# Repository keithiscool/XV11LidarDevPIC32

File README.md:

This project uses the XV11 Lidar from a Neato Vacuum Cleaner to track a robot in an 4meter x 8meter arena
The object tracking uses the robot reflectance in order to only track reflective surfaces and objects that are far away from the walls
The MPLabX project "lidarpic_FloatingPoint.X" in the software folder uses a PIC32MX575F512H-80I/PT (ordered from Digikey) micro-controller running at 80MHz
The hardware PCB used is the "FAB_xv11_lidar_dev_2016_01_24" EagleCAD file located in the Hardware folder.

Note: you need to use an FTDI chip to debug the project.
Look at the 6 pin (looks like Arduino ISP header. 
FTDI board rx pin goes to Uart 6 on pic32
Ground goes to ground on the same 6 pin header

Next, run a serial debugger program on your pc like realterm, teraterm, arduino to debug the UART line from the pic32
Also double check the lidar is connected.
The headers are loose on the pic32 header for UART4. hook lidar brown/yellow wire (Lidar tx) to the pic32 (UART4RX). Hook up the lidar power and ground.

The MOSFET and Diode that are being pulsed use the circuit in the included PDF: "Lidar Development Using PIC32MX Microcontroller"
Next hook up the motor power to the +5V pin next to the air wired mosfet.
YOU WILL HAVE TO REPROGRAM THE pic32 when you first power it on with the pickit3 programmer. The pic32 will stop spinning the lidar until the pic32 is re-programmed.

I recommend you make the following changes for the Wii Camera/Lidar board.
1) Add 3.3V pin for Wii Cameras
2) Choose a pic32MX with more independent timers (1 or 2 more 16 bit timers) - the pic32 only has 4 independent timers
3) Switching buck converters (switching down power converters) to help with battery efficiency
4) Add more output capacitance for voltage LDO regulators if you do not use a switching regulator
5) Beef up 3.3V trace on board
6) Place 5V power for lidar next to lidar input pins (place +5V next to UA4RX)

7) Choose an isolated mosfet driver (the one we used was not isolated (grounds were tied  too much noise)
8) Integrate a large mosfet onto the board and use the mosfet driver with it with the attached circuit (see attachment)
9) Choosing locking connectors OR solder all wires to board
10) Move programming header closer to pic32 and avoid meandering traces under & over board

Recommendations:
11) Add a non-ultrasonic distance meter to help with backing up the robot
12) Get ultra-reflective surfaces for TRACEE to help with LIDAR (Aluminum reflectance varied too much from 70 to 130 quality)
13) Use a Gimbal/gyro on the Lidar to help keep it level with arena sand
14) Lower Lidar to sit in the arena like I left it (this will prevent false positives from the judges
15) Look into dust tolerance methods for Lidar (static electricity/magnetism/sound vibrations/solenoid)

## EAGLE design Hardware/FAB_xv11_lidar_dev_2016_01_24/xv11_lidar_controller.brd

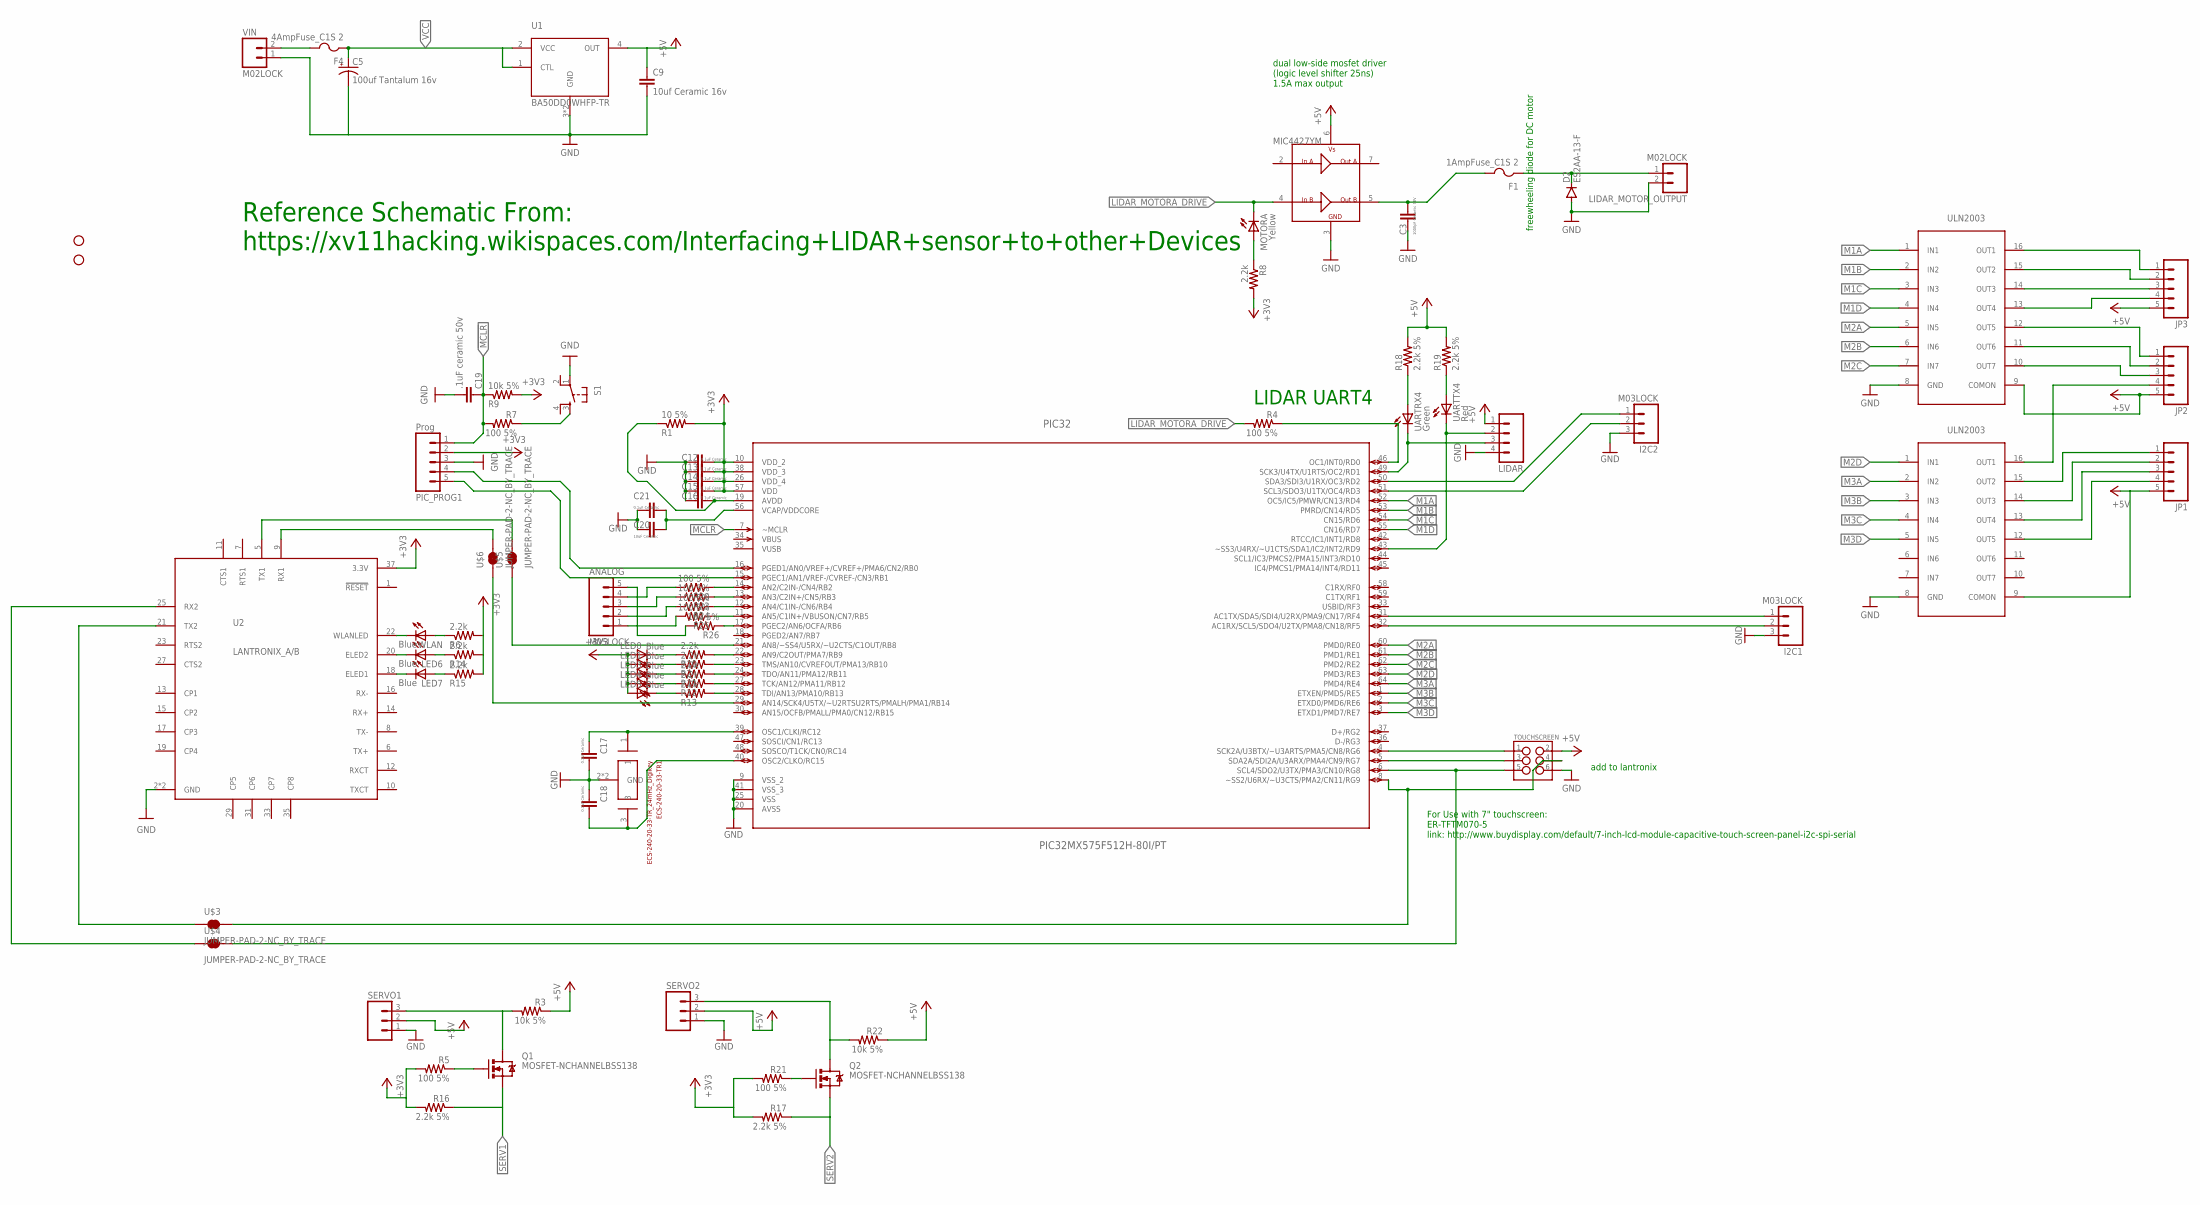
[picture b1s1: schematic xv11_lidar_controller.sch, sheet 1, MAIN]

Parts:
ANALOG: M05LOCK; 1X05_LOCK
C3: 1000pF Ceramic 50V; 0805
C5: 100uf Tantalum 16v; EIA3216
C9: 10uf Ceramic 16v; 0805
C12, C13, C14, C15, C16, C17, C18, C21: 0.1uF Ceramic; 0805
C19: .1uF ceramic 50v; 0805
C20: 10uF Ceramic; 0805
D2: ES2AA-13-F; SMA-DIODE
ECS-240-20-33-TR1: ECS-240-20-33-TR_24mHz_Digikey; ECX-32
F1: 1AmpFuse_C1S 2; R1206
F4: 4AmpFuse_C1S 2; R1206
I2C1, I2C2: M03LOCK; 1X03_LOCK
JP1, JP2, JP3: M05LOCK; 1X05_LOCK
LED0, LED1, LED3, LED4, LED5, LED6, LED7: Blue; CHIP-LED0805
LIDAR: M04LOCK; 1X04_LOCK
LIDAR_MOTOR_OUTPUT: M02LOCK; 1X02_LOCK
MOTORA: Yellow; CHIP-LED0805
PIC32: PIC32MX575F512H-80I/PT; QFP50P1200X1200X120-64N
PIC_PROG1: Prog; 1X05_LOCK_LONGPADS
Q1, Q2: MOSFET-NCHANNELBSS138; SOT23
R1: 10 5%; R0805
R2, R6, R10, R11, R12, R13, R14, R15: 2.2k; R0805
R3, R9, R22: 10k 5%; R0805
R4: 100 5%; M0805
R5, R7, R20, R21, R23, R24, R25, R26: 100 5%; R0805
R8: 2.2k; M0805
R16, R17: 2.2k 5%; R0805
R18, R19: 2.2k 5%; M0805
S1: TAC_SWITCHSMD; TACTILE-SWITCH-SMD
SERVO1, SERVO2: M03PTH; 1X03
STANDOFF1, STANDOFF2: STAND-OFF
TOUCHSCREEN: M03X2NO_SILK; 2X3-NS
U1: BA50DD0WHFP-TR; HRP5
U2: LANTRONIX_A/B; LANA/BTH
U3: MIC4427YM; SO-08
U$1, U$2: ULN2003; SOIC16_3.9WIDE
U$3, U$4, U$5, U$6: JUMPER-PAD-2-NC_BY_TRACE; PAD-JUMPER-2-NC_BY_TRACE_YES_SILK
UARTRX4: Green; CHIP-LED0805
UARTTX4: Red; CHIP-LED0805
VIN: M02LOCK; 1X02_LOCK
WLAN: Blue; CHIP-LED0805

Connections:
!MCLR: C19.1, PIC32.7 (~MCLR), PIC_PROG1.1, R7.2, R9.1
+3V3: C12.2, C13.2, C14.2, C15.2, LED0.A, LED1.A, LED3.A, LED4.A, LED5.A, PIC32.10 (VDD_2), PIC32.26 (VDD_4), PIC32.38 (VDD_3), PIC32.57 (VDD), PIC_PROG1.2, R1.2, R5.2, R6.2, R8.2, R9.2, R14.2, R15.2, R16.2, R17.2, R21.2, U2.37 (3.3V); also elsewhere on the board
+5V: C9.1, JP1.5, JP2.5, JP3.5, LIDAR.1, R3.1, R18.2, R19.2, R22.1, SERVO1.2, SERVO2.2, TOUCHSCREEN.2, U1.4 (OUT), U3.6 (VS), U$1.9 (COMON), U$2.9 (COMON)
GND: C3.1, C5.C (-), C9.2, C12.1, C13.1, C14.1, C15.1, C16.1, C17.2, C18.1, C19.2, C20.1, C21.1, D2.A, ECS-240-20-33-TR1.2 (GND), ECS-240-20-33-TR1.4 (GND), I2C1.3, I2C2.3, LIDAR.4, LIDAR_MOTOR_OUTPUT.2, PIC32.9 (VSS_2), PIC32.20 (AVSS), PIC32.25 (VSS), PIC32.41 (VSS_3), PIC_PROG1.3, S1.1, SERVO1.1, SERVO2.1, TOUCHSCREEN.6, U1.3 (GND), U1.G (GND), U2.2 (GND), U2.39 (GND), U3.3 (GND), U$1.8 (GND), U$2.8 (GND), VIN.1; also elsewhere on the board
LIDAR_MOTORA_DRIVE: MOTORA.C, R4.2, U3.4 (INB)
LIDAR_MOTOR_OUTPUT: D2.C, F1.1, LIDAR_MOTOR_OUTPUT.1
M1A: PIC32.52 (OC5/IC5/PMWR/CN13/RD4), U$1.1 (IN1)
M1B: PIC32.53 (PMRD/CN14/RD5), U$1.2 (IN2)
M1C: PIC32.54 (CN15/RD6), U$1.3 (IN3)
M1D: PIC32.55 (CN16/RD7), U$1.4 (IN4)
M2A: PIC32.60 (PMD0/RE0), U$1.5 (IN5)
M2B: PIC32.61 (PMD1/RE1), U$1.6 (IN6)
M2C: PIC32.62 (PMD2/RE2), U$1.7 (IN7)
M2D: PIC32.63 (PMD3/RE3), U$2.1 (IN1)
M3A: PIC32.64 (PMD4/RE4), U$2.2 (IN2)
M3B: PIC32.1 (ETXEN/PMD5/RE5), U$2.3 (IN3)
M3C: PIC32.2 (ETXD0/PMD6/RE6), U$2.4 (IN4)
M3D: PIC32.3 (ETXD1/PMD7/RE7), U$2.5 (IN5)
N1: PIC32.22 (AN9/C2OUT/PMA7/RB9), R10.2
N2: PIC32.23 (TMS/AN10/CVREFOUT/PMA13/RB10), R2.2
unnamed: U2.25 (RX2), U$4.1
unnamed: ANALOG.1, R25.2
unnamed: ANALOG.2, R24.2
unnamed: C3.2, F1.2, U3.5 (OUTB)
unnamed: PIC32.46 (OC1/INT0/RD0), R4.1
unnamed: PIC32.14 (AN2/C2IN-/CN4/RB2), R20.1
unnamed: U2.21 (TX2), U$3.1
unnamed: R18.1, UARTRX4.A
unnamed: ANALOG.3, R23.2
unnamed: PIC32.13 (AN3/C2IN+/CN5/RB3), R23.1
unnamed: C17.1, ECS-240-20-33-TR1.1, PIC32.39 (OSC1/CLKI/RC12)
unnamed: C18.2, ECS-240-20-33-TR1.3, PIC32.40 (OSC2/CLKO/RC15)
unnamed: PIC32.12 (AN4/C1IN-/CN6/RB4), R24.1
unnamed: PIC32.11 (AN5/C1IN+/VBUSON/CN7/RB5), R25.1
unnamed: ANALOG.4, R20.2
unnamed: C16.2, PIC32.19 (AVDD), R1.1
unnamed: C20.2, C21.2, PIC32.56 (VCAP/VDDCORE)
unnamed: Q1.3 (D), R3.2, SERVO1.3
unnamed: PIC32.16 (PGED1/AN0/VREF+/CVREF+/PMA6/CN2/RB0), PIC_PROG1.4
unnamed: LED0.C, R10.1
unnamed: PIC32.8 (~SS2/U6RX/~U3CTS/PMA2/CN11/RG9), TOUCHSCREEN.4, U$3.2
unnamed: LED1.C, R2.1
unnamed: R7.1, S1.3
unnamed: LED3.C, R11.1
unnamed: Q2.3 (D), R22.2, SERVO2.3
unnamed: Q1.1 (G), R5.1
unnamed: Q2.1 (G), R21.1
unnamed: LIDAR.3, PIC32.49 (SCK3/U4TX/U1RTS/OC2/RD1), UARTRX4.C
unnamed: LIDAR.2, PIC32.43 (~SS3/U4RX/~U1CTS/SDA1/IC2/INT2/RD9), UARTTX4.C
unnamed: MOTORA.A, R8.1
unnamed: PIC32.24 (TDO/AN11/PMA12/RB11), R11.2
unnamed: PIC32.17 (PGEC2/AN6/OCFA/RB6), R26.1
unnamed: ANALOG.5, R26.2
unnamed: U2.9 (RX1), U$6.2
unnamed: PIC32.21 (AN8/~SS4/U5RX/~U2CTS/C1OUT/RB8), U$5.1
unnamed: R19.1, UARTTX4.A
unnamed: F4.2, VIN.2
unnamed: JP3.1, U$1.16 (OUT1)
unnamed: JP3.2, U$1.15 (OUT2)
unnamed: JP3.3, U$1.14 (OUT3)
unnamed: JP3.4, U$1.13 (OUT4)
unnamed: JP2.1, U$1.12 (OUT5)
unnamed: JP2.2, U$1.11 (OUT6)
unnamed: JP2.3, U$1.10 (OUT7)
unnamed: JP2.4, U$2.16 (OUT1)
unnamed: JP1.1, U$2.15 (OUT2)
unnamed: JP1.2, U$2.14 (OUT3)
unnamed: JP1.3, U$2.13 (OUT4)
unnamed: JP1.4, U$2.12 (OUT5)
unnamed: U2.5 (TX1), U$5.2
unnamed: I2C2.1, PIC32.50 (SDA3/SDI3/U1RX/OC3/RD2)
unnamed: I2C2.2, PIC32.51 (SCL3/SDO3/U1TX/OC4/RD3)
unnamed: PIC32.29 (AN14/SCK4/U5TX/~U2RTSU2RTS/PMALH/PMA1/R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), U$6.1
unnamed: U2.22 (WLANLED), WLAN.C
unnamed: LED6.C, U2.20 (ELED2)
unnamed: LED7.C, U2.18 (ELED1)
unnamed: LED7.A, R15.1
unnamed: LED6.A, R14.1
unnamed: R6.1, WLAN.A
ONE: LED5.C, R13.1
PICUART_RX: I2C1.1, PIC32.31 (AC1TX/SDA5/SDI4/U2RX/PMA9/CN17/RF4)
PICUART_TX: I2C1.2, PIC32.32 (AC1RX/SCL5/SDO4/U2TX/PMA8/CN18/RF5)
PIC_HANG_CHK: PIC32.15 (PGEC1/AN1/VREF-/CVREF-/CN3/RB1), PIC_PROG1.5
SCK2: PIC32.4 (SCK2A/U3BTX/~U3ARTS/PMA5/CN8/RG6), TOUCHSCREEN.1
SDI2: PIC32.5 (SDA2A/SDI2A/U3ARX/PMA4/CN9/RG7), TOUCHSCREEN.3
SDO2: PIC32.6 (SCL4/SDO2/U3TX/PMA3/CN10/RG8), TOUCHSCREEN.5, U$4.2
SERV1: PIC32.28 (TDI/AN13/PMA10/RB13), Q1.2 (S), R13.2, R16.1
SERV2: PIC32.27 (TCK/AN12/PMA11/RB12), Q2.2 (S), R12.2, R17.1
TWO: LED4.C, R12.1
VCC: C5.A (+), F4.1, U1.1 (CTL), U1.2 (VCC); also elsewhere on the board
VUSB: PIC32.35 (VUSB)

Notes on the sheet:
Reference Schematic From: https://xv11hacking.wikispaces.com/Interfacing+LIDAR+sensor+to+other+Devices
freewheeling diode for DC motor
LIDAR UART4
dual low-side mosfet driver (logic level shifter 25ns) 1.5A max output
For Use with 7" touchscreen: ER-TFTM070-5 link: http://www.buydisplay.com/default/7-inch-lcd-module-capacitive-touch-screen-panel-i2c-spi-serial
add to lantronix

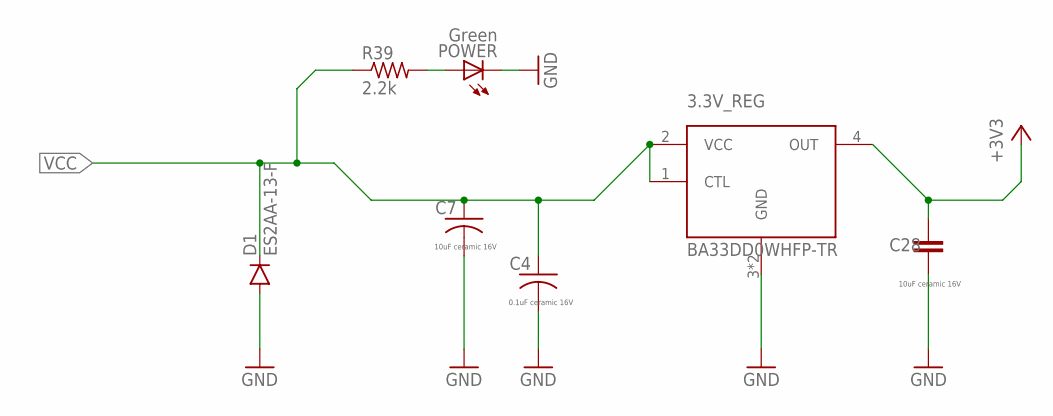
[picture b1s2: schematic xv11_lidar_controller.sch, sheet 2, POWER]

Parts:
3.3V_REG: BA33DD0WHFP-TR; HRP5
C4: 0.1uF ceramic 16V; C0805K
C7: 10uF ceramic 16V; C0805K
C28: 10uF ceramic 16V; 0805
D1: ES2AA-13-F; SMA-DIODE
POWER: Green; CHIP-LED0805
R39: 2.2k; R0805

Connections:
+3V3: 3.3V_REG.4 (OUT), C28.1; also elsewhere on the board
GND: 3.3V_REG.3 (GND), 3.3V_REG.G (GND), C4.2, C7.2, C28.2, D1.A, POWER.C; also elsewhere on the board
unnamed: POWER.A, R39.2
VCC: 3.3V_REG.1 (CTL), 3.3V_REG.2 (VCC), C4.1, C7.1, D1.C, R39.1; also elsewhere on the board

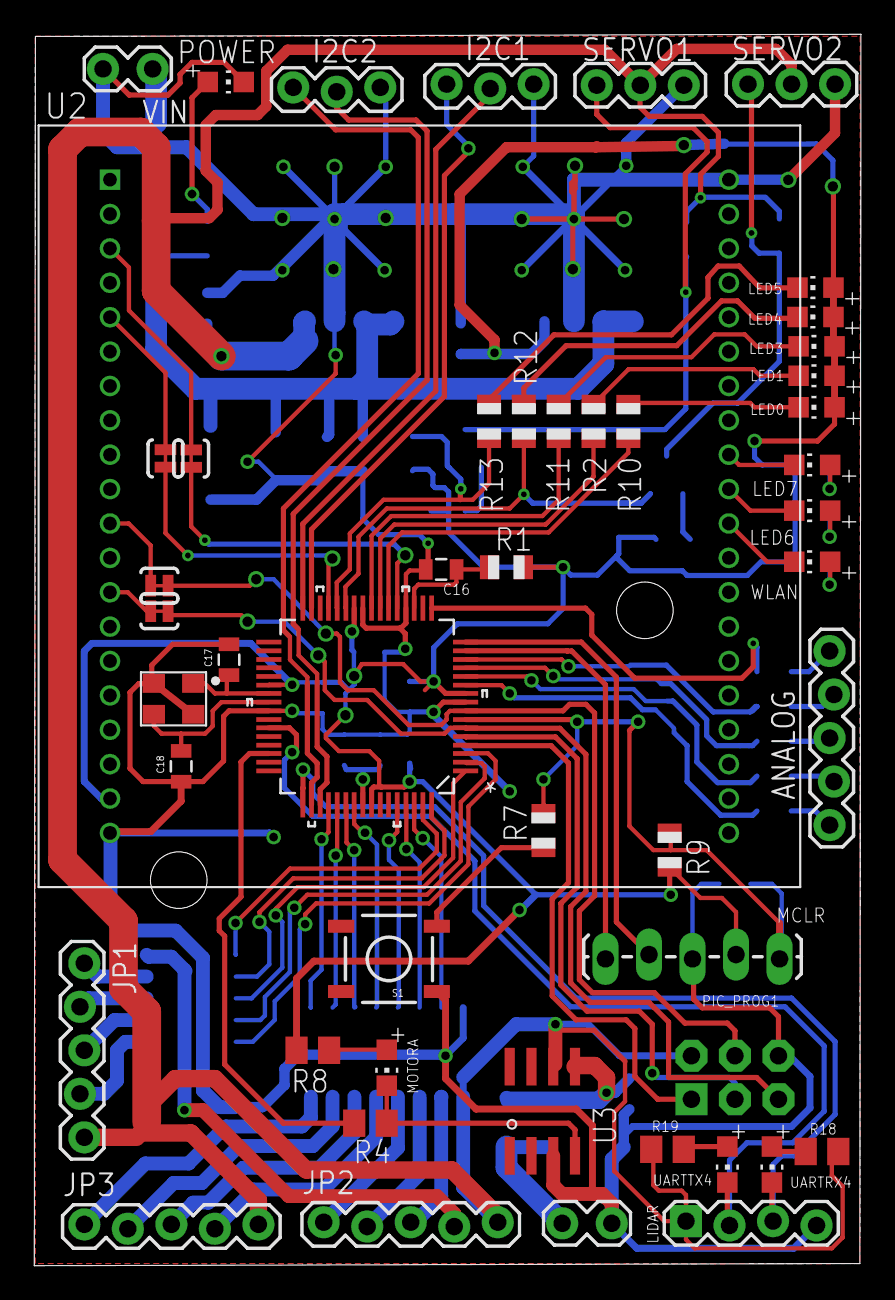
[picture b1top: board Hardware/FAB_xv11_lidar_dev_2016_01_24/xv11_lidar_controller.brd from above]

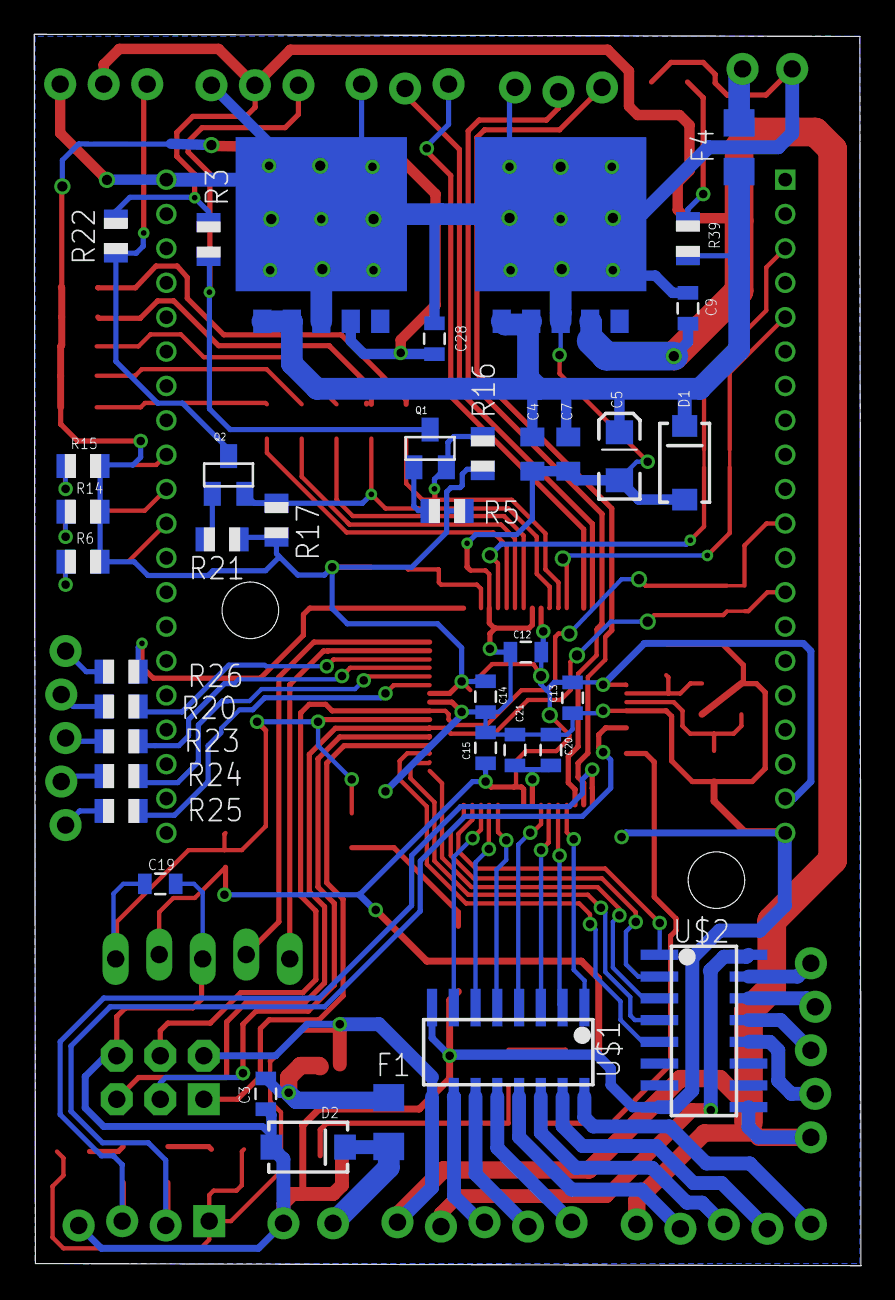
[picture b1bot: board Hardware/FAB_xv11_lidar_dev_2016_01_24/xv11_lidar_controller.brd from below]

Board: 2 copper layers, 48.2 x 71.9 mm, 89 parts (38 on the bottom side), 91 nets.

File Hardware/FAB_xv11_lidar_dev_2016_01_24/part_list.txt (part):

Partlist

Exported from xv11_lidar_controller.brd at 4/28/2016 9:19:55 PM

EAGLE Version 6.5.0 Copyright (c) 1988-2013 CadSoft

Assembly variant: 

Part               Value                          Package                           Library                        Position (mil)        Orientation

3.3V_REG           BA33DD0WHFP-TR                 HRP5                              NASA_LIB                       (1240 2170)           MR0
ANALOG             M05LOCK                        1X05_LOCK                         SparkFun-Connectors            (1832.5 1012.5)       R90
C3                 1000pF Ceramic 50V             0805                              SparkFun-Capacitors            (1367.5 395)          MR90
C4                 0.1uF ceramic 16V              C0805K                            adafruit                       (755 1865)            MR270
C5                 100uf Tantalum 16v             EIA3216                           SparkFun-Capacitors            (555 1860)            MR90
C7                 10uF ceramic 16V               C0805K                            adafruit                       (672.5 1865)          MR270
C9                 10uf Ceramic 16v               0805                              SparkFun-Capacitors            (397.5 2200)          MR90
C12                0.1uF Ceramic                  0805                              SparkFun-Capacitors            (770 1410)            MR0
C13                0.1uF Ceramic                  0805                              SparkFun-Capacitors            (662.5 1305)          MR90
C14                0.1uF Ceramic                  0805                              SparkFun-Capacitors            (862.5 1307.5)        MR90
C15                0.1uF Ceramic                  0805                              SparkFun-Capacitors            (862.5 1190)          MR270
C16                0.1uF Ceramic                  0805                              SparkFun-Capacitors            (935 1600)            R0
C17                0.1uF Ceramic                  0805                              SparkFun-Capacitors            (447.5 1392.5)        R90
C18                0.1uF Ceramic                  0805                              SparkFun-Capacitors            (337.5 1147.5)        R90
C19                .1uF ceramic 50v               0805                              SparkFun-Capacitors            (1610 877.5)          MR0
C20                10uF Ceramic                   0805                              SparkFun-Capacitors            (712.5 1185)          MR270
C21                0.1uF Ceramic                  0805                              SparkFun-Capacitors            (795 1185)            MR270
C28                10uF ceramic 16V               0805                              SparkFun-Capacitors            (980 2130)            MR90
D1                 ES2AA-13-F                     SMA-DIODE                         SparkFun-DiscreteSemi          (405 1845)            MR90
D2                 ES2AA-13-F                     SMA-DIODE                         SparkFun-DiscreteSemi          (1270 272.5)          MR0
ECS-240-20-33-TR1  ECS-240-20-33-TR_24mHz_Digikey ECX-32                            Crystal ECS                    (320 1302.5)          R180
F1                 1AmpFuse_C1S 2                 R1206                             adafruit                       (1085 330)            MR90
F4                 4AmpFuse_C1S 2                 R1206                             adafruit                       (280 2570)            MR90
I2C1               M03LOCK                        1X03_LOCK                         SparkFun-Connectors            (947.5 2710)          R0
I2C2               M03LOCK                        1X03_LOCK                         SparkFun-Connectors            (595 2702.5)          R0
JP1                                               1X05_LOCK                         SparkFun-Connectors            (110 695)             R270
JP2                                               1X05_LOCK                         SparkFun-Connectors            (665 95)              R0
JP3                                               1X05_LOCK                         SparkFun-Connectors            (115 90)              R0
LED0               Blue                           CHIP-LED0805                      adafruit                       (1797.5 1972.5)       R90
LED1               Blue                           CHIP-LED0805                      adafruit                       (1797.5 2045)         R90
LED3               Blue                           CHIP-LED0805                      adafruit                       (1797.5 2112.5)       R90
LED4               Blue                           CHIP-LED0805                      adafruit                       (1795 2180)           R90
LED5               Blue                           CHIP-LED0805                      adafruit                       (1795 2247.5)         R90
LED6               Blue                           CHIP-LED0805                      adafruit                       (1787.5 1735)         R90
LED7               Blue                           CHIP-LED0805                      adafruit                       (1787.5 1840)         R90
LIDAR                                             1X04_LOCK                         SparkFun-Connectors            (1497.5 97.5)         R0
LIDAR_MOTOR_OUTPUT M02LOCK                        1X02_LOCK                         SparkFun-Connectors            (1220 97.5)           R0
MOTORA             Yellow                         CHIP-LED0805                      adafruit                       (810 455)             R180
PIC32              PIC32MX575F512H-80I/PT         QFP50P1200X1200X120-64N           Microchip_By_element14_Batch_1 (765 1285)            R180
PIC_PROG1          Prog                           1X05_LOCK_LONGPADS                SparkFun-Connectors            (1712.5 705)          R180
POWER              Green                          CHIP-LED0805                      adafruit                       (440 2720)            R270
Q1                 MOSFET-NCHANNELBSS138          SOT23                             SparkFun-DiscreteSemi          (990 1878)            MR0
Q2                 MOSFET-NCHANNELBSS138          SOT23                             SparkFun-DiscreteSemi          (1453 1817)           MR0
R1                 10 5%                          R0805                             adafruit                       (1085 1605)           R0
R2                 2.2k                           R0805                             adafruit                       (1285 1940)           R270
R3                 10k 5%                         R0805                             adafruit                       (1499 2358)           MR270
R4                 100 5%                         M0805                             adafruit                       (772.5 327.5)         R0
R5                 100 5%                         R0805                             adafruit                       (951 1734)            MR0
R6                 2.2k                           R0805                             adafruit                       (1787.5 1617.5)       MR0
R7                 100 5%                         R0805                             adafruit                       (1170 1000)           R90
R8                 2.2k                           M0805                             adafruit                       (640 495)             R180
R9                 10k 5%                         R0805                             adafruit                       (1460 955)            R270
R10                2.2k                           R0805                             adafruit                       (1365 1940)           R270
R11                2.2k                           R0805                             adafruit                       (1205 1940)           R270
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
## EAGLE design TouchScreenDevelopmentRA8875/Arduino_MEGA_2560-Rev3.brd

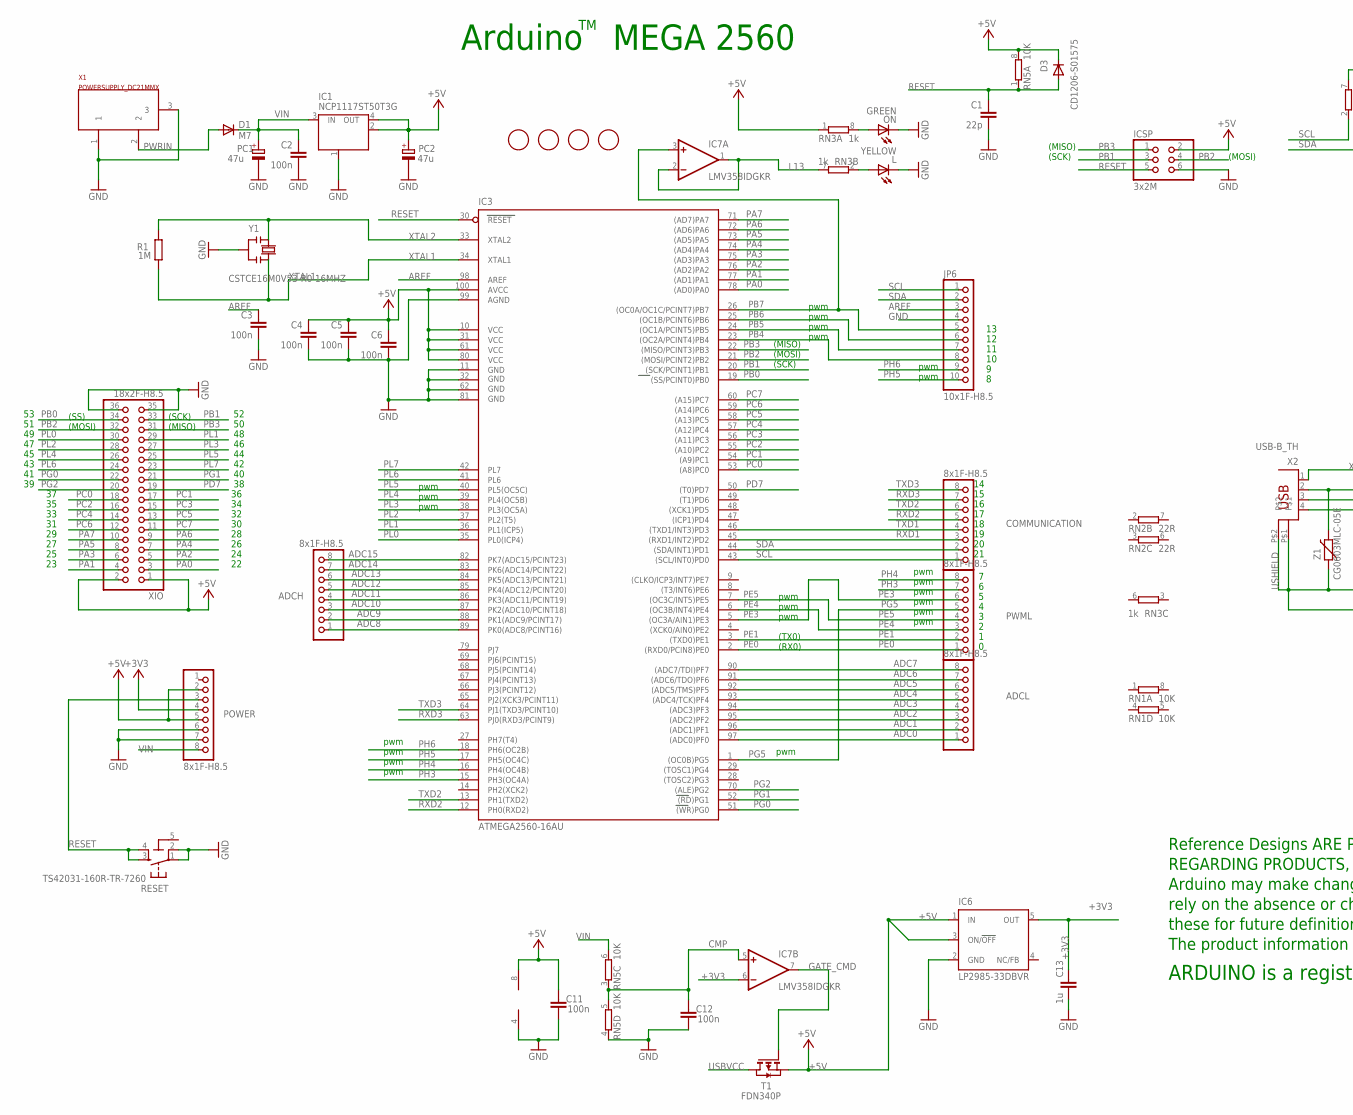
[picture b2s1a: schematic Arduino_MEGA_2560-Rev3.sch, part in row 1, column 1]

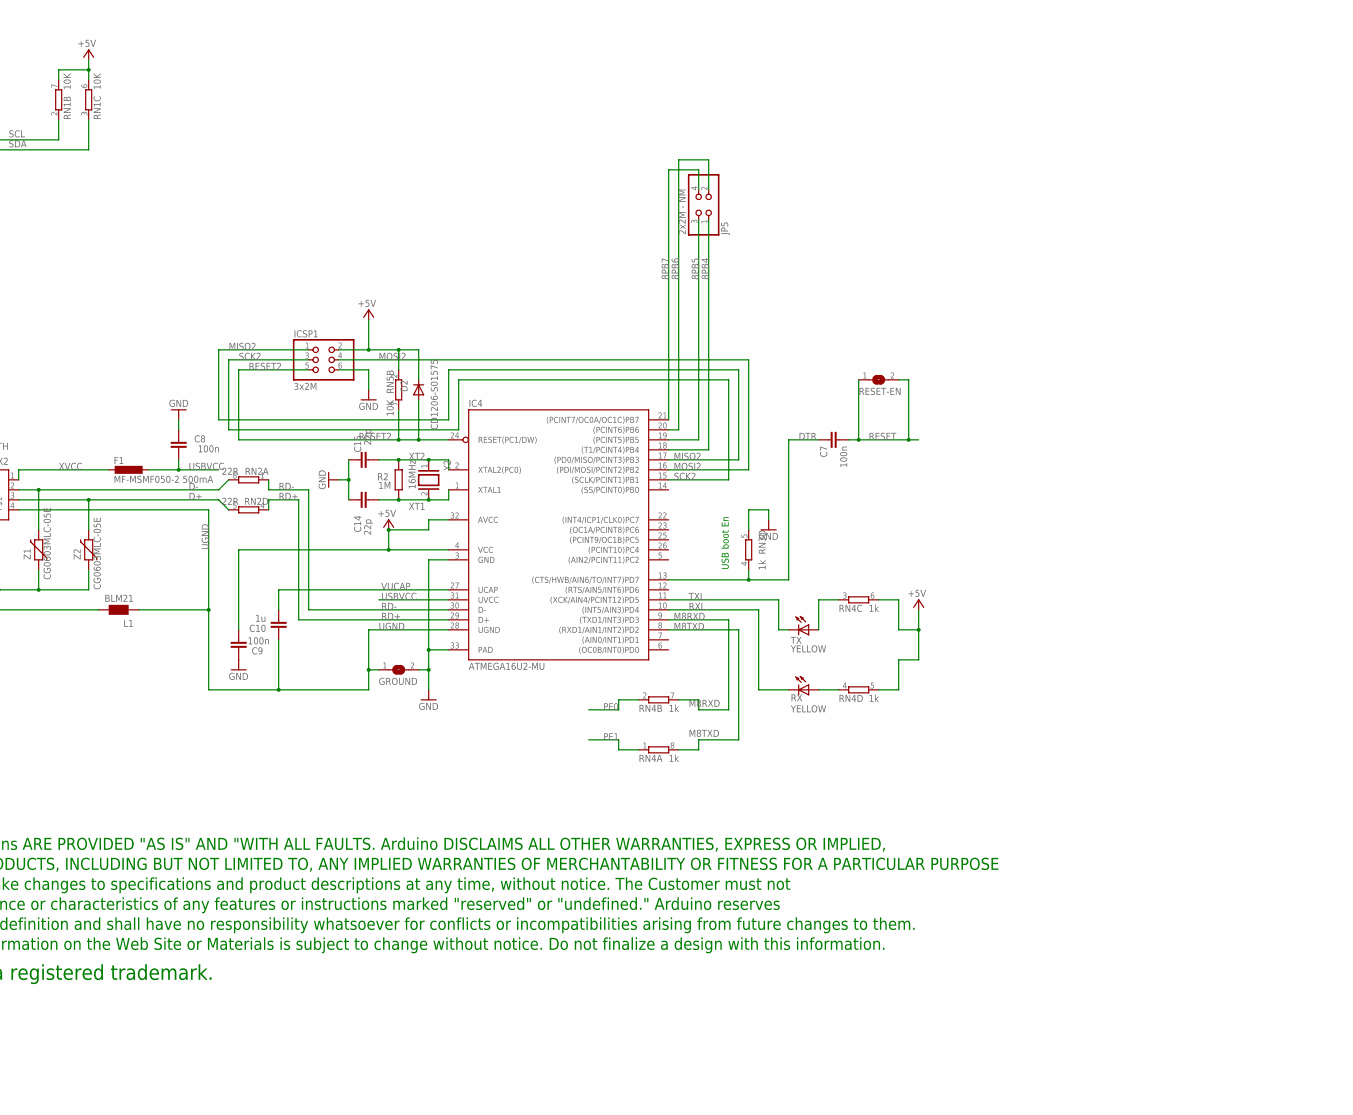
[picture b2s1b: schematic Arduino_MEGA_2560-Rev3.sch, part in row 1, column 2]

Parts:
ADCH: 8x1F-H8.5; 1X08
ADCL: 8x1F-H8.5; 1X08
C1, C14, C15: 22p; C0603-ROUND
C2, C3, C4, C5, C6, C7, C8, C9, C11, C12: 100n; C0603-ROUND
C10, C13: 1u; C0603-ROUND
COMMUNICATION: 8x1F-H8.5; 1X08
D1: M7; SMB
D2, D3: CD1206-S01575; MINIMELF
F1: MF-MSMF050-2 500mA; L1812
FD1, FD2, FD3, FD4: FIDUCIALMOUNT; FIDUCIA-MOUNT
GROUND: SJ
IC1: NCP1117ST50T3G; SOT223
IC3: ATMEGA2560-16AU; TQFP100
IC4: ATMEGA16U2-MU; MLF32
IC6: LP2985-33DBVR; SOT23-DBV
IC7: LMV358IDGKR; MSOP08
ICSP, ICSP1: 3x2M; 2X03
JP5: 2x2M - NM; 2X02
JP6: 10x1F-H8.5; 1X10
L: YELLOW; CHIP-LED0805
L1: BLM21; 0805
ON: GREEN; CHIP-LED0805
PC1, PC2: 47u; PANASONIC_D
POWER: 8x1F-H8.5; 1X08
PWML: 8x1F-H8.5; 1X08
R1, R2: 1M; R0603-ROUND
RESET: TS42031-160R-TR-7260; TS42
RESET-EN: SJ
RN1, RN5: 10K; CAT16
RN2: 22R; CAY16
RN3, RN4: 1k; CAY16
RX: YELLOW; CHIP-LED0805
T1: FDN340P; SOT-23
TX: YELLOW; CHIP-LED0805
U$1: DISCLAIMER
X1: POWERSUPPLY_DC21MMX; POWERSUPPLY_DC-21MM
X2: USB-B_TH; PN61729
XIO: 18x2F-H8.5; 2X18
Y1: CSTCE16M0V53-R0 16MHZ; RESONATOR
Y2: 16MHz; QS
Z1, Z2: CG0603MLC-05E; CT/CN0603

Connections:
5-GND: RESET.5 (5-GND)
8PB4: IC4.18 ((T1/PCINT4)PB4), JP5.1
8PB5: IC4.19 ((PCINT5)PB5), JP5.3
8PB6: IC4.20 ((PCINT6)PB6), JP5.2
8PB7: IC4.21 ((PCINT7/OC0A/OC1C)PB7), JP5.4
+3V3: C13.2, IC6.5 (OUT), IC7.6 (-IN), POWER.4
+5V: C4.1, C5.1, C6.1, C9.1, C11.2, D2.C, D3.C, IC1.2 (OUT), IC1.4 (OUT), IC3.10 (VCC), IC3.31 (VCC1), IC3.61 (VCC2), IC3.80 (VCC3), IC3.100 (AVCC), IC4.4 (VCC), IC4.32 (AVCC), IC6.1 (IN), IC6.3 (ON/!OFF), IC7.8 (V+), ICSP.2, ICSP1.2, PC2.+, POWER.2, POWER.5, RN1.6 (2), RN1.7 (2), RN3.1, RN4.5 (2), RN4.6 (2), RN5.2 (1), RN5.8 (2), T1.2 (S), XIO.1, XIO.2
ADC0: ADCL.1, IC3.97 ((ADC0)PF0)
ADC1: ADCL.2, IC3.96 ((ADC1)PF1)
ADC2: ADCL.3, IC3.95 ((ADC2)PF2)
ADC3: ADCL.4, IC3.94 ((ADC3)PF3)
ADC4: ADCL.5, IC3.93 ((ADC4/TCK)PF4)
ADC5: ADCL.6, IC3.92 ((ADC5/TMS)PF5)
ADC6: ADCL.7, IC3.91 ((ADC6/TDO)PF6)
ADC7: ADCL.8, IC3.90 ((ADC7/TDI)PF7)
ADC8: ADCH.1, IC3.89 (PK0(ADC8/PCINT16))
ADC9: ADCH.2, IC3.88 (PK1(ADC9/PCINT17))
ADC10: ADCH.3, IC3.87 (PK2(ADC10/PCINT18))
ADC11: ADCH.4, IC3.86 (PK3(ADC11/PCINT19))
ADC12: ADCH.5, IC3.85 (PK4(ADC12/PCINT20))
ADC13: ADCH.6, IC3.84 (PK5(ADC13/PCINT21))
ADC14: ADCH.7, IC3.83 (PK6(ADC14/PCINT22))
ADC15: ADCH.8, IC3.82 (PK7(ADC15/PCINT23))
AREF: C3.1, IC3.98 (AREF), JP6.3
CMP: C12.2, IC7.5 (+IN), RN5.3 (1), RN5.5 (2)
D+: RN2.5 (2), X2.3, Z2.2
D-: RN2.8 (2), X2.2, Z1.2
DTR: C7.1, IC4.13 ((CTS/HWB/AIN6/TO/INT7)PD7), RN3.4 (1)
GATE_CMD: IC7.7 (OUT), T1.3 (G)
GND: C1.2, C2.2, C3.2, C4.2, C5.2, C6.2, C8.2, C9.2, C11.1, C12.1, C13.1, C14.2, C15.2, GROUND.2, IC1.1 (GND/ADJ), IC3.11 (GND), IC3.32 (GND1), IC3.62 (GND2), IC3.81 (GND3), IC3.99 (AGND), IC4.3 (GND), IC4.33 (PAD), IC6.2 (GND), IC7.4 (V-), ICSP.6, ICSP1.6, JP6.4, L.C, ON.C, PC1.-, PC2.-, POWER.6, POWER.7, RESET.1, RESET.2, RN3.5 (2), RN5.4 (1), X1.1, X1.3, XIO.35, XIO.36, Y1.2
L13: IC7.1 (OUT), IC7.2 (-IN), RN3.7 (2)
M8RXD: IC4.9 ((TXD1/INT3)PD3), RN4.7 (2)
M8TXD: IC4.8 ((RXD1/AIN1/INT2)PD2), RN4.8 (2)
MISO2: IC4.17 ((PD0/MISO/PCINT3)PB3), ICSP1.1
MOSI2: IC4.16 ((PDI/MOSI/PCINT2)PB2), ICSP1.4
unnamed: L.A, RN3.2 (1)
unnamed: ON.A, RN3.8 (2)
unnamed: RN4.4 (1), RX.A
unnamed: RN4.3 (1), TX.A
PA0: IC3.78 ((AD0)PA0), XIO.3
PA1: IC3.77 ((AD1)PA1), XIO.4
PA2: IC3.76 ((AD2)PA2), XIO.5
PA3: IC3.75 ((AD3)PA3), XIO.6
PA4: IC3.74 ((AD4)PA4), XIO.7
PA5: IC3.73 ((AD5)PA5), XIO.8
PA6: IC3.72 ((AD6)PA6), XIO.9
PA7: IC3.71 ((AD7)PA7), XIO.10
PB0: IC3.19 ((SS/PCINT0)PB0), XIO.34
PB1: IC3.20 ((SCK/PCINT1)PB1), ICSP.3, XIO.33
PB2: IC3.21 ((MOSI/PCINT2)PB2), ICSP.4, XIO.32
PB3: IC3.22 ((MISO/PCINT3)PB3), ICSP.1, XIO.31
PB4: IC3.23 ((OC2A/PCINT4)PB4), JP6.8
PB5: IC3.24 ((OC1A/PCINT5)PB5), JP6.7
PB6: IC3.25 ((OC1B/PCINT6)PB6), JP6.6
PB7: IC3.26 ((OC0A/OC1C/PCINT7)PB7), IC7.3 (+IN), JP6.5
PC0: IC3.53 ((A8)PC0), XIO.18
PC1: IC3.54 ((A9)PC1), XIO.17
PC2: IC3.55 ((A10)PC2), XIO.16
PC3: IC3.56 ((A11)PC3), XIO.15
PC4: IC3.57 ((A12)PC4), XIO.14
PC5: IC3.58 ((A13)PC5), XIO.13
PC6: IC3.59 ((A14)PC6), XIO.12
PC7: IC3.60 ((A15)PC7), XIO.11
PD7: IC3.50 ((T0)PD7), XIO.19
PE0: IC3.2 ((RXD0/PCIN8)PE0), PWML.1, RN4.2 (1)
PE1: IC3.3 ((TXD0)PE1), PWML.2, RN4.1
PE3: IC3.5 ((OC3A/AIN1)PE3), PWML.6
PE4: IC3.6 ((OC3B/INT4)PE4), PWML.3
PE5: IC3.7 ((OC3C/INT5)PE5), PWML.4
PG0: IC3.51 ((WR)PG0), XIO.22
PG1: IC3.52 ((RD)PG1), XIO.21
PG2: IC3.70 ((ALE)PG2), XIO.20
PG5: IC3.1 ((OC0B)PG5), PWML.5
PH3: IC3.15 (PH3(OC4A)), PWML.7
PH4: IC3.16 (PH4(OC4B)), PWML.8
PH5: IC3.17 (PH5(OC4C)), JP6.10
PH6: IC3.18 (PH6(OC2B)), JP6.9
PL0: IC3.35 (PL0(ICP4)), XIO.30
PL1: IC3.36 (PL1(ICP5)), XIO.29
PL2: IC3.37 (PL2(T5)), XIO.28
PL3: IC3.38 (PL3(OC5A)), XIO.27
PL4: IC3.39 (PL4(OC5B)), XIO.26
PL5: IC3.40 (PL5(OC5C)), XIO.25
PL6: IC3.41 (PL6), XIO.24
PL7: IC3.42 (PL7), XIO.23
PWRIN: D1.A, X1.2
RD+: IC4.29 (D+), RN2.4 (1)
RD-: IC4.30 (D-), RN2.1
RESET: C1.1, C7.2, D3.A, IC3.30 (RESET), ICSP.5, POWER.3, RESET.3, RESET.4, RESET-EN.1, RESET-EN.2, RN5.1
RESET2: D2.A, IC4.24 (RESET(PC1/DW)), ICSP1.5, RN5.7 (2)
RXD1: COMMUNICATION.3, IC3.45 ((RXD1/INT2)PD2)
RXD2: COMMUNICATION.5, IC3.12 (PH0(RXD2))
RXD3: COMMUNICATION.7, IC3.63 (PJ0(RXD3/PCINT9))
RXL: IC4.10 ((INT5/AIN3)PD4), RX.C
SCK2: IC4.15 ((SCLK/PCINT1)PB1), ICSP1.3
SCL: COMMUNICATION.1, IC3.43 ((SCL/INT0)PD0), JP6.1, RN1.2 (1)
SDA: COMMUNICATION.2, IC3.44 ((SDA/INT1)PD1), JP6.2, RN1.3 (1)
TXD1: COMMUNICATION.4, IC3.46 ((TXD1/INT3)PD3)
TXD2: COMMUNICATION.6, IC3.13 (PH1(TXD2))
TXD3: COMMUNICATION.8, IC3.64 (PJ1(TXD3/PCINT10))
TXL: IC4.11 ((XCK/AIN4/PCINT12)PD5), TX.C
UGND: C10.2, GROUND.1, IC4.28 (UGND), L1.1, X2.4
USBVCC: C8.1, F1.1, IC4.31 (UVCC), T1.1 (D)
USHIELD: L1.2, X2.P$1, X2.P$2, Z1.1, Z2.1
VIN: C2.1, D1.C, IC1.3 (IN), PC1.+, POWER.8, RN5.6 (2)
VUCAP: C10.1, IC4.27 (UCAP)
XT1: C14.1, IC4.1 (XTAL1), R2.1, Y2.2
XT2: C15.1, IC4.2 (XTAL2(PC0)), R2.2, Y2.1
XTAL1: IC3.34 (XTAL1), R1.1, Y1.3
XTAL2: IC3.33 (XTAL2), R1.2, Y1.1
XVCC: F1.2, X2.1

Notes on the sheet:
Arduino MEGA 2560
(SCK)
(MISO)
(MOSI)
pwm
(TX0)
(RX0)
(SS)
USB boot En

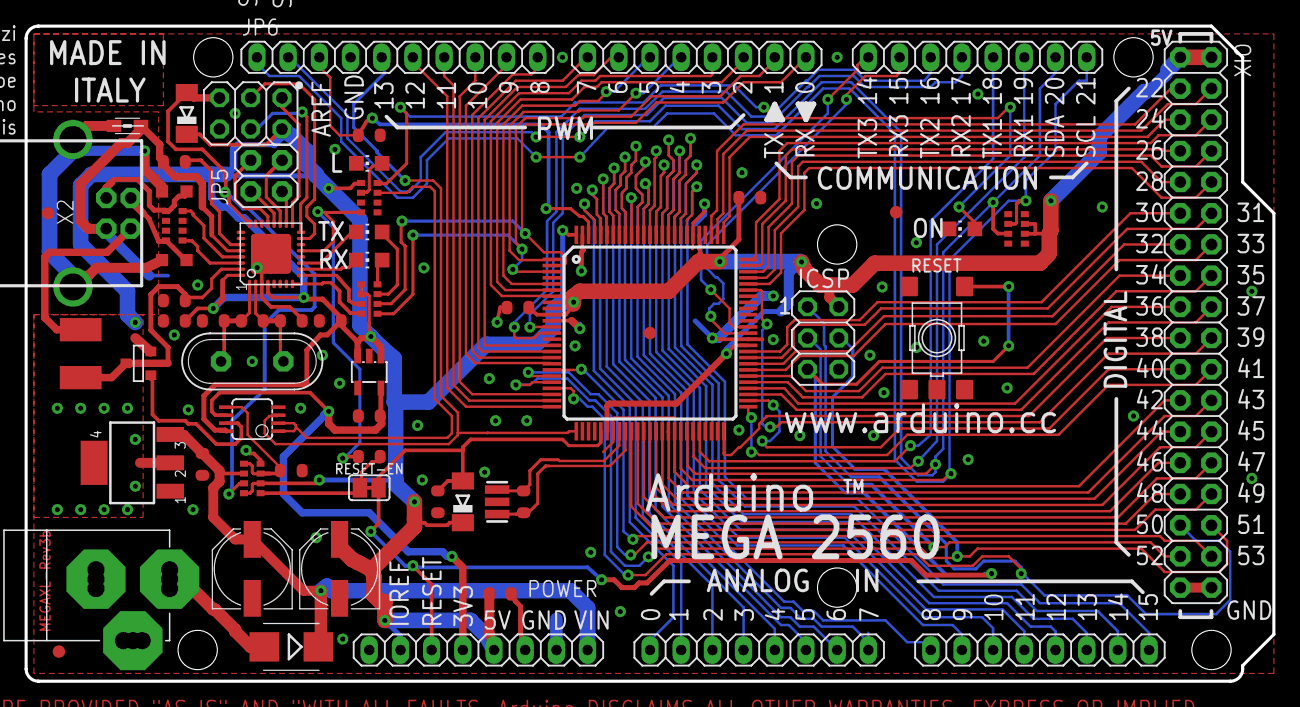
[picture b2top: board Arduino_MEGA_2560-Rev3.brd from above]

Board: 2 copper layers, 101.6 x 53.3 mm, 63 parts (1 on the bottom side), 110 nets.

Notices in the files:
parts and their libraries:
SparkFun-Connectors: Licensing: CC v3.0 Share-Alike You are welcome to use this library for commercial purposes.
SparkFun-Electromechanical: Licensing: Creative Commons ShareAlike 4.0 International - https://creativecommons.org/licenses/by-sa/4.0
